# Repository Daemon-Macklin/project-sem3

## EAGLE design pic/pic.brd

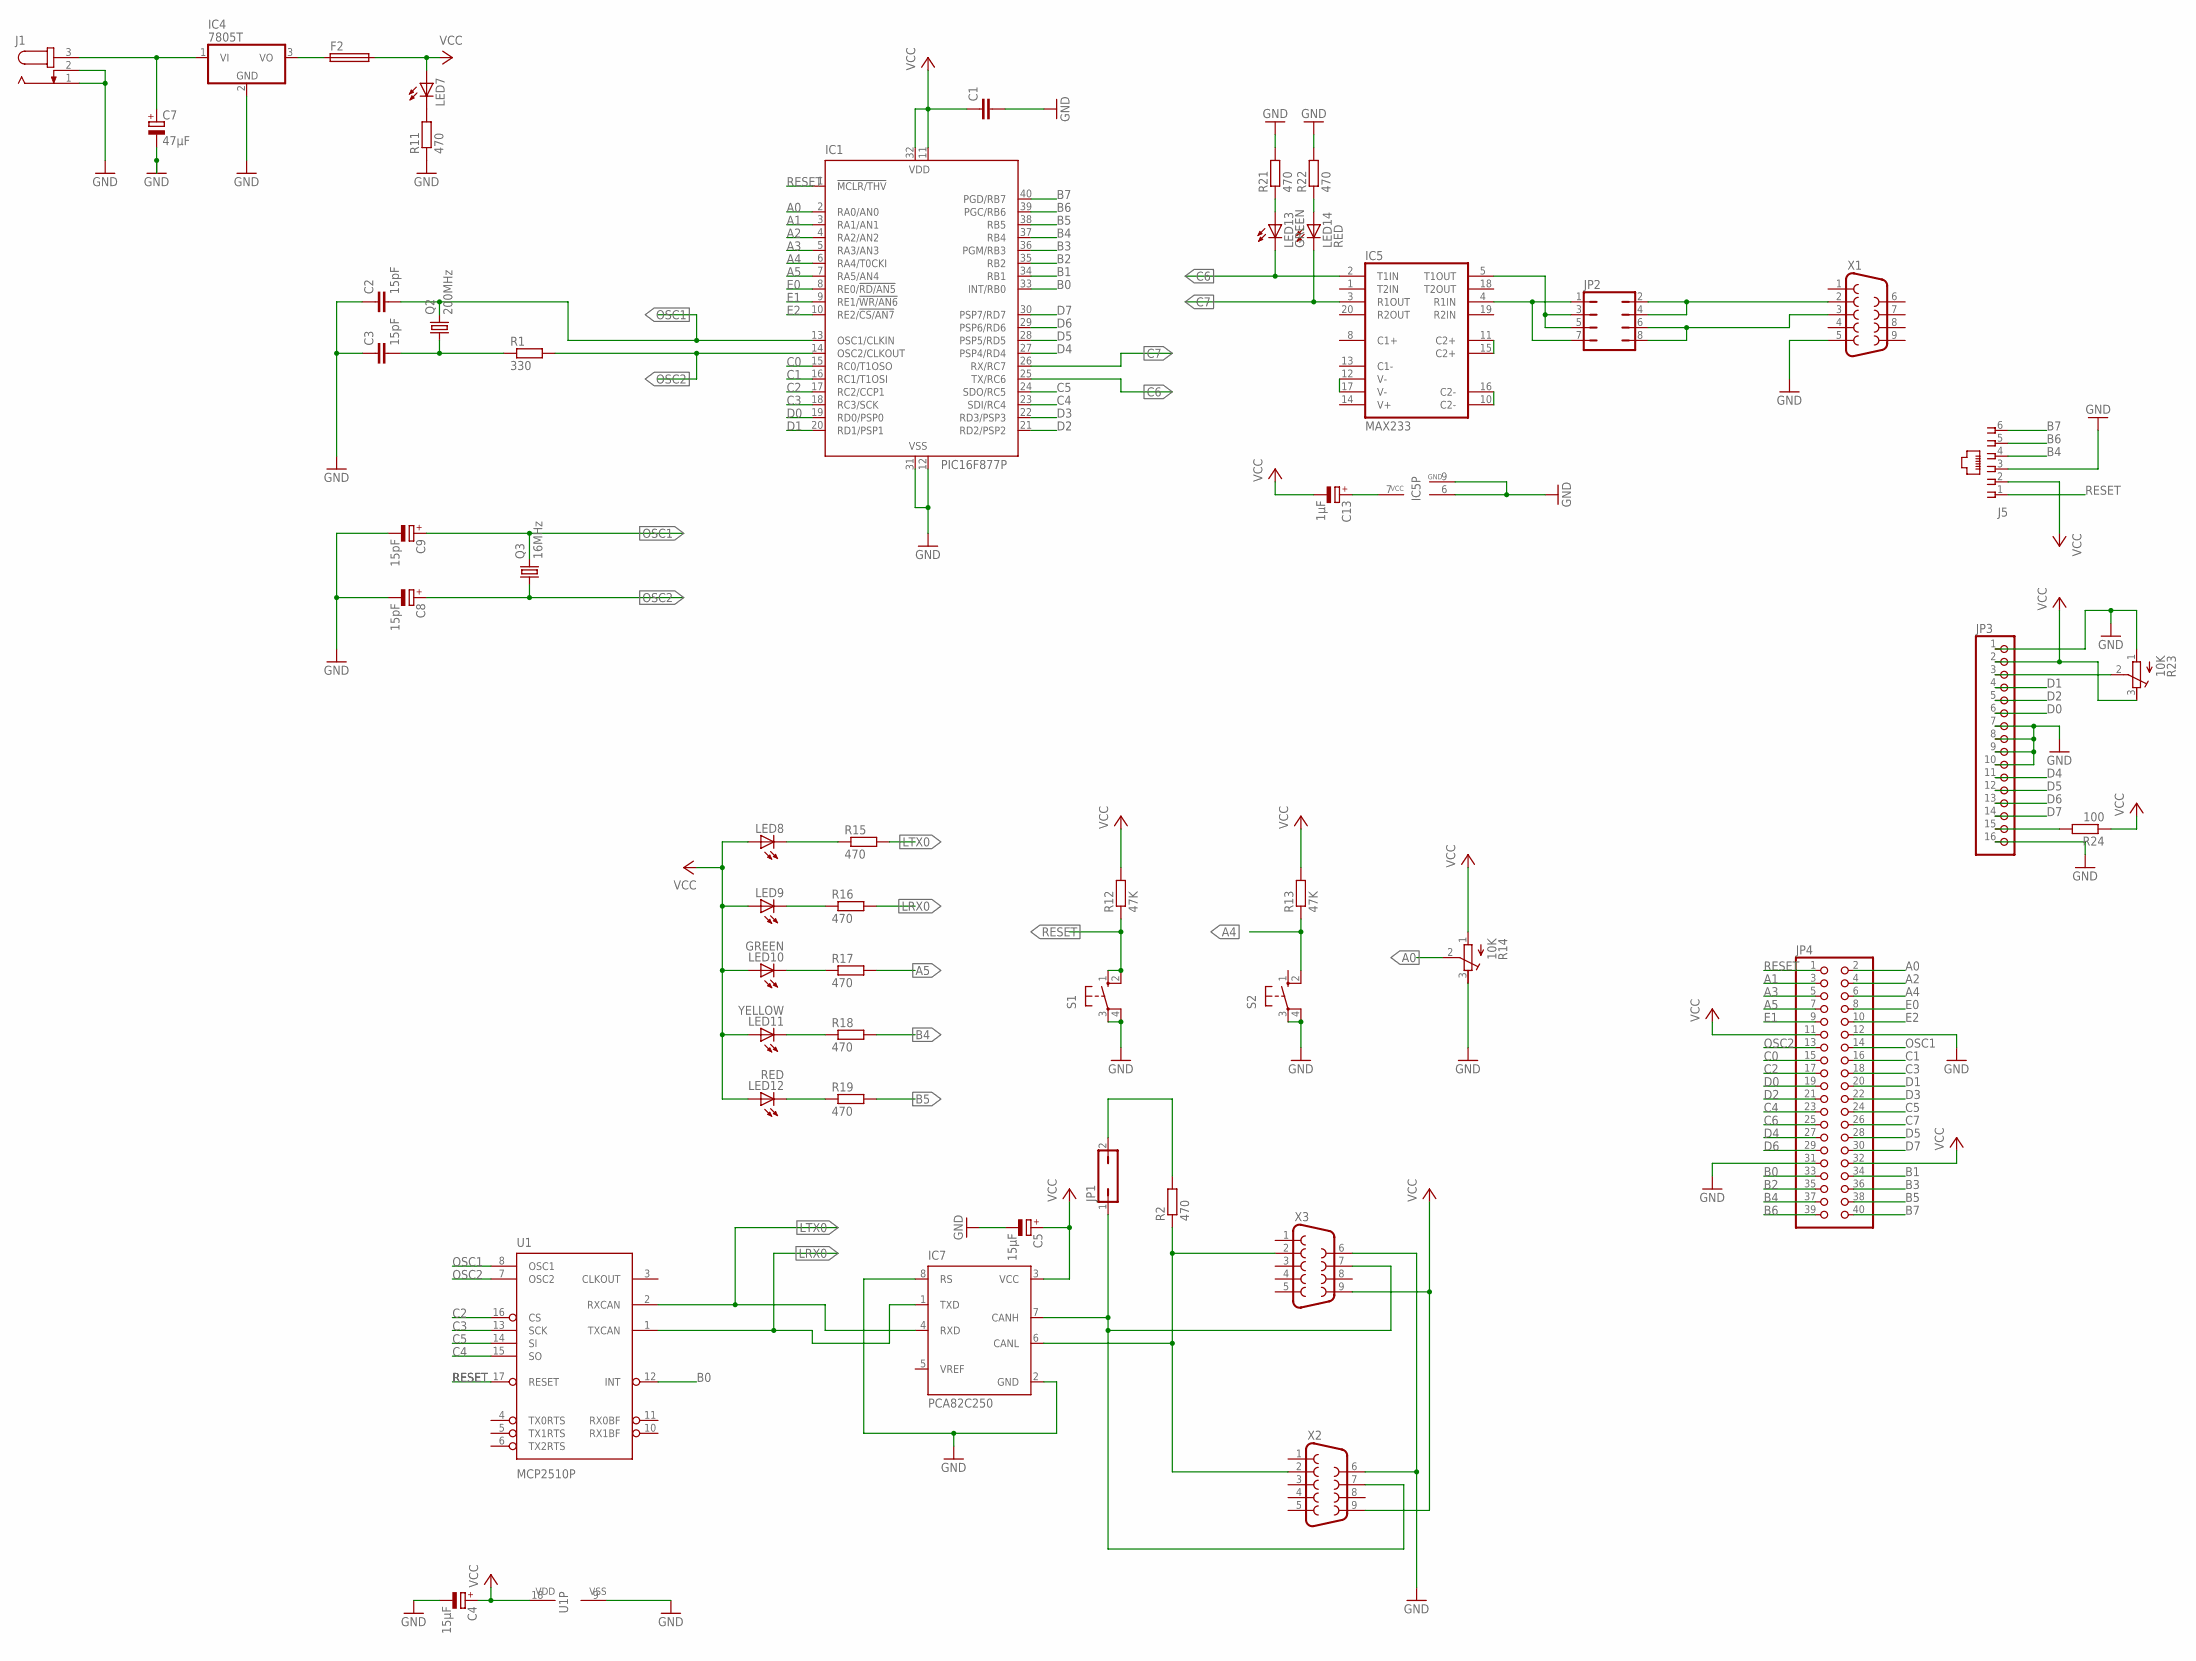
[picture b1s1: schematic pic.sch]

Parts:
C1: C5/5.5; C5B5.5
C2, C3: 15pF; C5B5.5
C4, C5: 15μF; E2,5-5
C7: 47μF; E2,5-5
C8, C9: 15pF; E2,5-5
C13: 1μF; E2,5-5
F2: F457
IC1: PIC16F877P; DIL40
IC4: 7805T; TO220H
IC5: MAX233; DIL20
IC7: PCA82C250; DIL08
J1: JACK-PLUG1; SPC4078
J5: 520243-3
JP1: JP1Q; JP1
JP2: JP4Q
JP3: PINHD-1X16; 1X16
JP4: PINHD-2X20; 2X20
LED7, LED8, LED9: LED5MM
LED10, LED13: GREEN; LED5MM
LED11: YELLOW; LED5MM
LED12, LED14: RED; LED5MM
Q2: 200MHz; HC49U-H
Q3: 16MHz; HC49U-H
R1: 330; 0207/10
R2, R11, R15, R16, R17, R18, R19, R21, R22: 470; 0207/10
R12, R13: 47K; 0207/10
R14, R23: 10K; RTRIM3296X
R24: 100; 0207/10
S1, S2: 10-XX; B3F-10XX
U1: MCP2510P; DIL18
X1, X2, X3: F09HP

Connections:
A0: IC1.2 (RA0/AN0), JP4.2, R14.2 (S)
A1: IC1.3 (RA1/AN1), JP4.3
A2: IC1.4 (RA2/AN2), JP4.4
A3: IC1.5 (RA3/AN3), JP4.5
A4: IC1.6 (RA4/T0CKI), JP4.6, R13.1, S2.2 (S1)
A5: IC1.7 (RA5/AN4), JP4.7, R17.2
B0: IC1.33 (INT/RB0), JP4.33, U1.12 (INT)
B1: IC1.34 (RB1), JP4.34
B2: IC1.35 (RB2), JP4.35
B3: IC1.36 (PGM/RB3), JP4.36
B4: IC1.37 (RB4), J5.4, JP4.37, R18.2
B5: IC1.38 (RB5), JP4.38, R19.2
B6: IC1.39 (PGC/RB6), J5.5, JP4.39
B7: IC1.40 (PGD/RB7), J5.6, JP4.40
C0: IC1.15 (RC0/T1OSO), JP4.15
C1: IC1.16 (RC1/T1OSI), JP4.16
C2: IC1.17 (RC2/CCP1), JP4.17, U1.16 (CS)
C3: IC1.18 (RC3/SCK), JP4.18, U1.13 (SCK)
C4: IC1.23 (SDI/RC4), JP4.23, U1.15 (SO)
C5: IC1.24 (SDO/RC5), JP4.24, U1.14 (SI)
C6: IC1.25 (TX/RC6), IC5.2 (T1IN), JP4.25, LED13.K (C)
C7: IC1.26 (RX/RC7), IC5.3 (R1OUT), JP4.26, LED14.K (C)
D0: IC1.19 (RD0/PSP0), JP3.6, JP4.19
D1: IC1.20 (RD1/PSP1), JP3.4, JP4.20
D2: IC1.21 (RD2/PSP2), JP3.5, JP4.21
D3: IC1.22 (RD3/PSP3), JP4.22
D4: IC1.27 (PSP4/RD4), JP3.11, JP4.27
D5: IC1.28 (PSP5/RD5), JP3.12, JP4.28
D6: IC1.29 (PSP6/RD6), JP3.13, JP4.29
D7: IC1.30 (PSP7/RD7), JP3.14, JP4.30
E0: IC1.8 (RE0/!RD/AN5), JP4.8
E1: IC1.9 (RE1/!WR/AN6), JP4.9
E2: IC1.10 (RE2/!CS/AN7), JP4.10
GND: C1.2, C2.1, C3.1, C4.-, C5.-, C7.-, C8.-, C9.-, IC1.12 (VSS), IC1.31 (VSS), IC4.2 (GND), IC5.6 (GND), IC5.9 (GND), IC7.2 (GND), IC7.8 (RS), J1.1, J1.2, J5.3, JP3.1, JP3.7, JP3.8, JP3.9, JP3.10, JP3.16, JP4.12, JP4.31, R11.1, R14.3 (E), R21.2, R22.2, R23.1 (A), S1.3, S1.4 (P1), S2.3, S2.4 (P1), U1.9 (VSS), X1.5, X2.6, X3.6
LRX0: IC7.1 (TXD), R16.2, U1.1 (TXCAN)
LTX0: IC7.4 (RXD), R15.2, U1.2 (RXCAN)
unnamed: JP1.2, R2.2
unnamed: C3.2, Q2.1, R1.1
unnamed: IC7.6 (CANL), R2.1, X2.2, X3.2
unnamed: IC7.7 (CANH), JP1.1, X2.7, X3.7
unnamed: C7.+, IC4.1 (VI), J1.3
unnamed: F2.1, IC4.3 (VO)
unnamed: LED7.K (C), R11.2
unnamed: IC5.4 (R1IN), JP2.1, JP2.7
unnamed: IC5.5 (T1OUT), JP2.3, JP2.5
unnamed: JP2.2, JP2.4, X1.2
unnamed: JP2.6, JP2.8, X1.3
unnamed: IC5.12 (V-), IC5.17 (V-)
unnamed: IC5.10 (C2-), IC5.16 (C2-)
unnamed: IC5.11 (C2+), IC5.15 (C2+)
unnamed: LED8.K (C), R15.1
unnamed: LED9.K (C), R16.1
unnamed: LED10.K (C), R17.1
unnamed: LED11.K (C), R18.1
unnamed: LED12.K (C), R19.1
unnamed: LED13.A, R21.1
unnamed: LED14.A, R22.1
unnamed: JP3.3, R23.2 (S)
unnamed: JP3.15, R24.2
unnamed: C13.+, IC5.7 (VCC)
OSC1: C2.2, C9.+, IC1.13 (OSC1/CLKIN), JP4.14, Q2.2, Q3.2, U1.8 (OSC1)
OSC2: C8.+, IC1.14 (OSC2/CLKOUT), JP4.13, Q3.1, R1.2, U1.7 (OSC2)
RESET: IC1.1 (!MCLR/THV), J5.1, JP4.1, R12.1, S1.1 (S), S1.2 (S1), U1.17 (RESET)
VCC: C1.1, C4.+, C5.+, C13.-, F2.2, IC1.11 (VDD), IC1.32 (VDD), IC7.3 (VCC), J5.2, JP3.2, JP4.11, JP4.32, LED7.A, LED8.A, LED9.A, LED10.A, LED11.A, LED12.A, R12.2, R13.2, R14.1 (A), R23.3 (E), R24.1, U1.18 (VDD), X2.9, X3.9

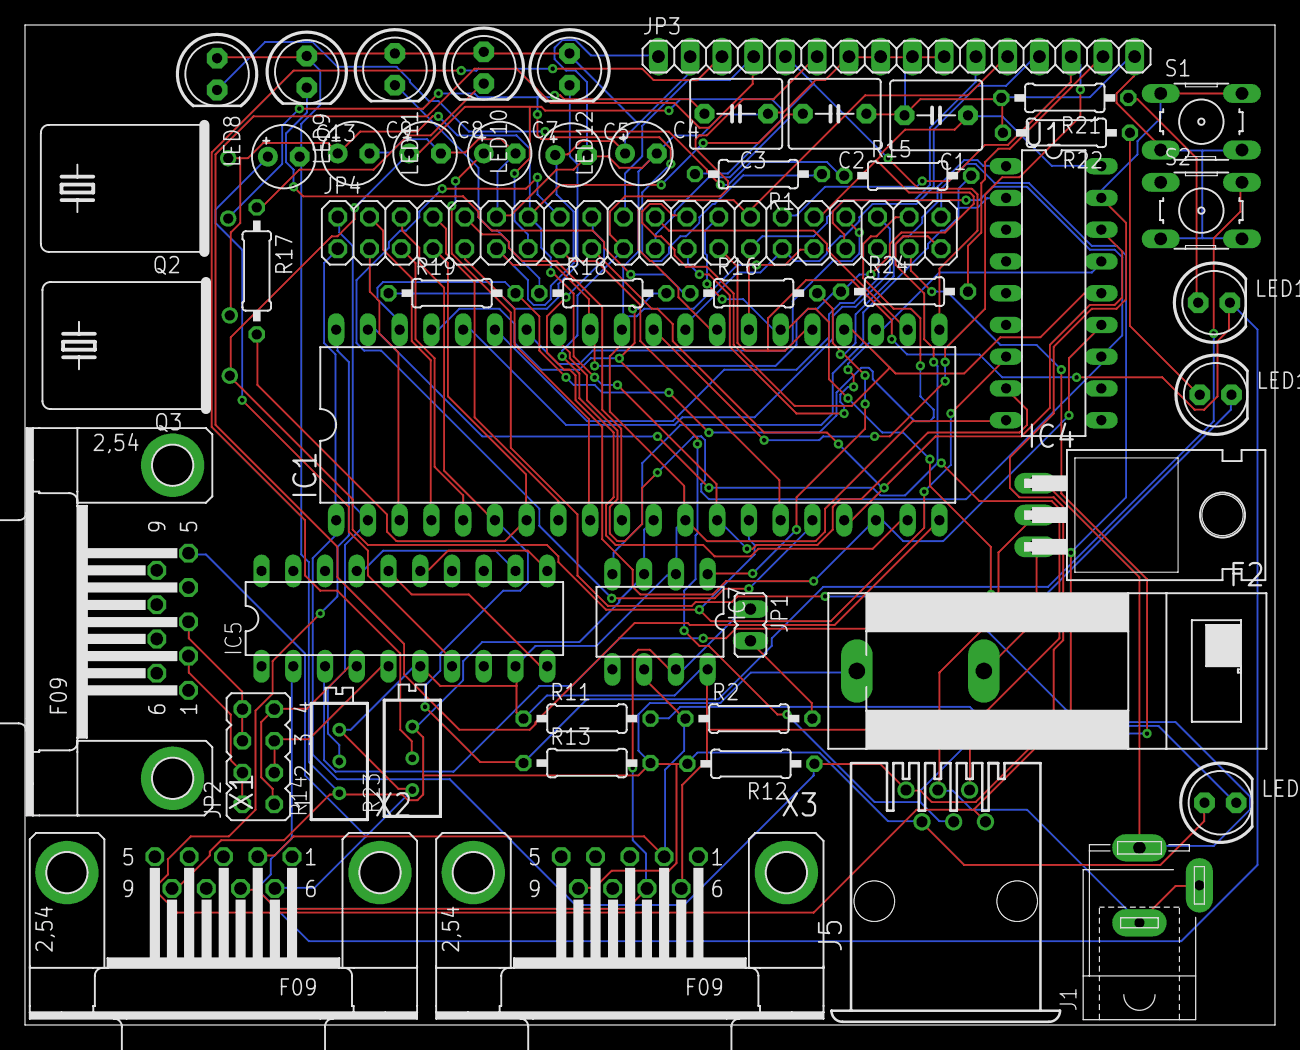
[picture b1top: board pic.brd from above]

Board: 2 copper layers, 100.0 x 80.0 mm, 51 parts (0 on the bottom side), 64 nets.

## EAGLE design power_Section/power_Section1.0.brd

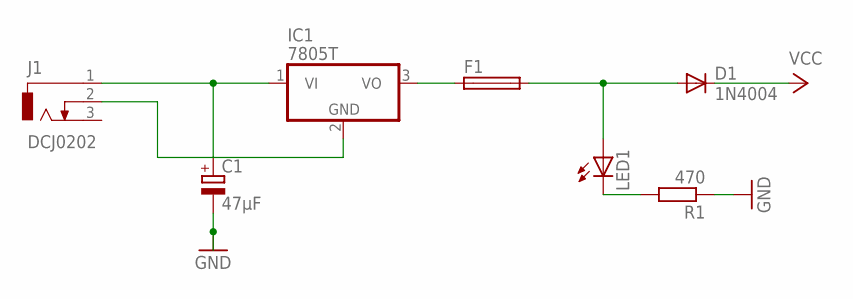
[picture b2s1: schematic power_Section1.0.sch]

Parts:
C1: 47μF; E2,5-5
D1: 1N4004; DO41-10
F1: F457
IC1: 7805T; TO220H
J1: DCJ0202
LED1: LED5MM
R1: 470; 0207/10

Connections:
GND: C1.-, R1.1
unnamed: C1.+, IC1.1 (VI), J1.1
unnamed: IC1.2 (GND), J1.2
unnamed: F1.1, IC1.3 (VO)
unnamed: D1.A, F1.2, LED1.A
unnamed: LED1.K (C), R1.2
VCC: D1.C

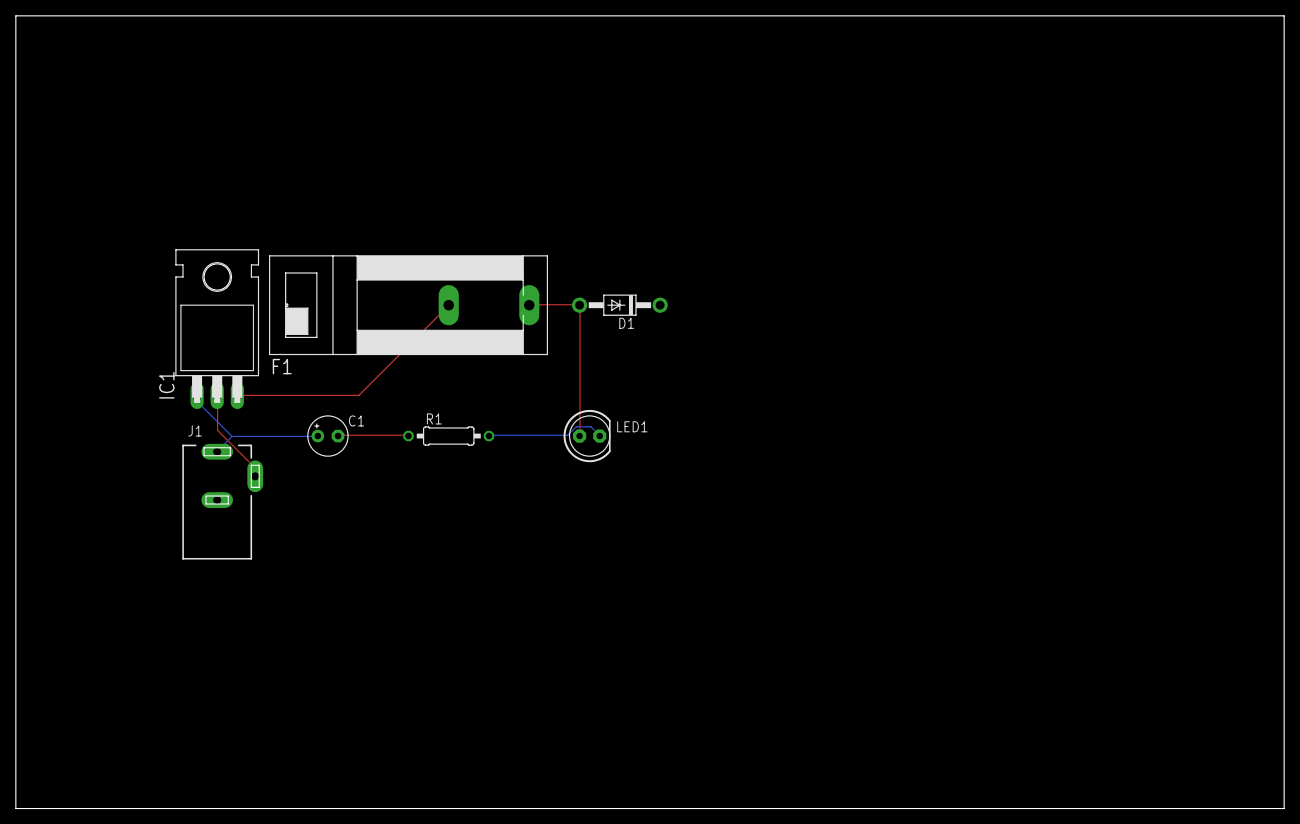
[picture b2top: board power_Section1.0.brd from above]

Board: 2 copper layers, 160.0 x 100.0 mm, 7 parts (0 on the bottom side), 6 nets.

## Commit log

2017-09-26 Schematic format update
2017-09-26 26/9/17 - LCD + PIC HEADER - EDITS TO RS232
2017-09-28 Finished Schematic
2017-10-05 Signed off netlist waiting check
2017-10-10 Updated board
